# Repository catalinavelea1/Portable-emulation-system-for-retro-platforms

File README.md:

# Portable-emulation-system-for-retro-platforms

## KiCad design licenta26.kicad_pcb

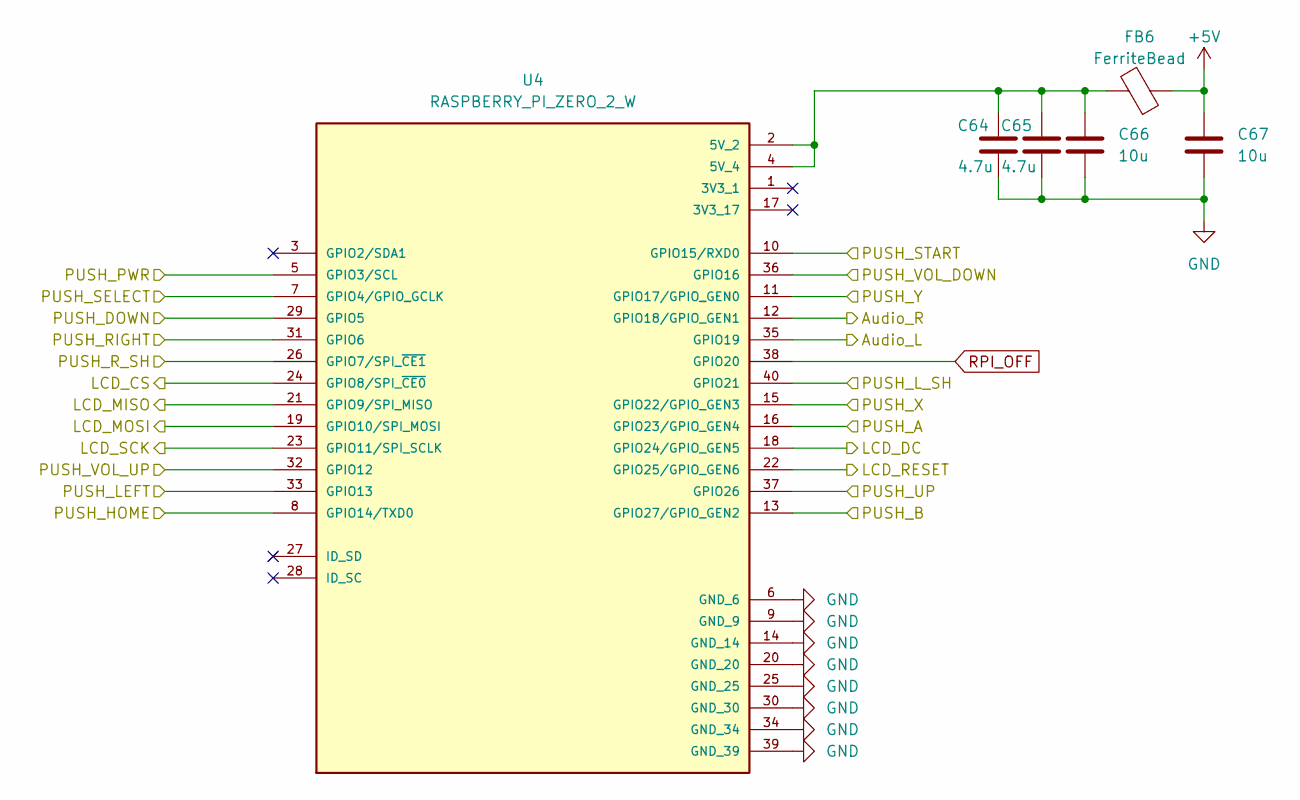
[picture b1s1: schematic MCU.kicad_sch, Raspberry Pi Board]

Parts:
C64, C65: 4.7u; C_1206_3216Metric_Pad1.33x1.80mm_HandSolder
C66, C67: 10u; C_1206_3216Metric_Pad1.33x1.80mm_HandSolder
FB6: FerriteBead; L_1206_3216Metric_Pad1.22x1.90mm_HandSolder
U4: RASPBERRY_PI_ZERO_2_W; MODULE_RASPBERRY_PI_ZERO_2_W; PARTREV April 2024

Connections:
/Audio_Sheet/Audio_L: U4.35 (GPIO19); also elsewhere on the board
/Audio_Sheet/Audio_R: U4.12 (GPIO18/GPIO_GEN1); also elsewhere on the board
/Buttons_Sheet/PUSH_A: U4.16 (GPIO23/GPIO_GEN4); also elsewhere on the board
/Buttons_Sheet/PUSH_B: U4.13 (GPIO27/GPIO_GEN2); also elsewhere on the board
/Buttons_Sheet/PUSH_DOWN: U4.29 (GPIO5); also elsewhere on the board
/Buttons_Sheet/PUSH_HOME: U4.8 (GPIO14/TXD0); also elsewhere on the board
/Buttons_Sheet/PUSH_LEFT: U4.33 (GPIO13); also elsewhere on the board
/Buttons_Sheet/PUSH_L_SH: U4.40 (GPIO21); also elsewhere on the board
/Buttons_Sheet/PUSH_RIGHT: U4.31 (GPIO6); also elsewhere on the board
/Buttons_Sheet/PUSH_R_SH: U4.26 (GPIO7/SPI_~CE1); also elsewhere on the board
/Buttons_Sheet/PUSH_SELECT: U4.7 (GPIO4/GPIO_GCLK); also elsewhere on the board
/Buttons_Sheet/PUSH_START: U4.10 (GPIO15/RXD0); also elsewhere on the board
/Buttons_Sheet/PUSH_UP: U4.37 (GPIO26); also elsewhere on the board
/Buttons_Sheet/PUSH_VOL_DOWN: U4.36 (GPIO16); also elsewhere on the board
/Buttons_Sheet/PUSH_VOL_UP: U4.32 (GPIO12); also elsewhere on the board
/Buttons_Sheet/PUSH_X: U4.15 (GPIO22/GPIO_GEN3); also elsewhere on the board
/Buttons_Sheet/PUSH_Y: U4.11 (GPIO17/GPIO_GEN0); also elsewhere on the board
/LCD_Sheet/LCD_CS: U4.24 (GPIO8/SPI_~CE0); also elsewhere on the board
/LCD_Sheet/LCD_DC: U4.18 (GPIO24/GPIO_GEN5); also elsewhere on the board
/LCD_Sheet/LCD_MISO: U4.21 (GPIO9/SPI_MISO); also elsewhere on the board
/LCD_Sheet/LCD_MOSI: U4.19 (GPIO10/SPI_MOSI); also elsewhere on the board
/LCD_Sheet/LCD_RESET: U4.22 (GPIO25/GPIO_GEN6); also elsewhere on the board
/LCD_Sheet/LCD_SCK: U4.23 (GPIO11/SPI_SCLK); also elsewhere on the board
/MCU/PUSH_PWR: U4.5 (GPIO3/SCL); also elsewhere on the board
GND: C64.2, C65.2, C66.2, C67.2, U4.6 (GND_6), U4.9 (GND_9), U4.14 (GND_14), U4.20 (GND_20), U4.25 (GND_25), U4.30 (GND_30), U4.34 (GND_34), U4.39 (GND_39); also elsewhere on the board
unnamed: C64.1, C65.1, C66.1, FB6.2, U4.2 (5V_2), U4.4 (5V_4)

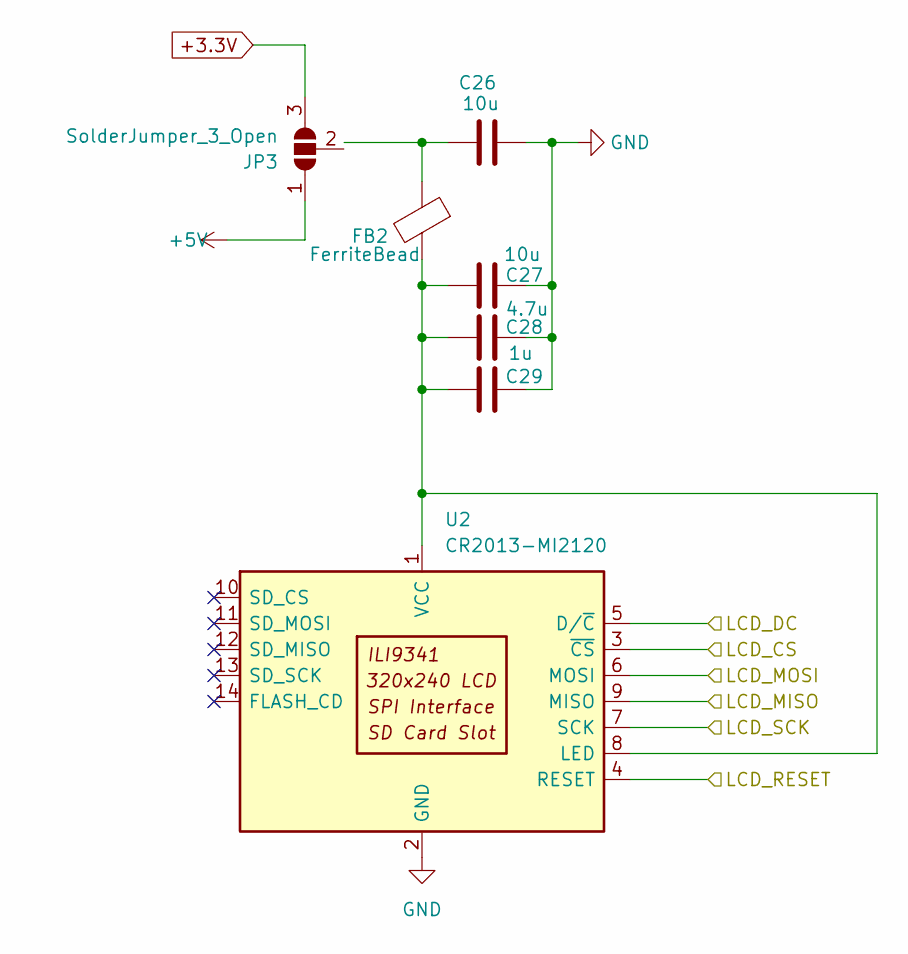
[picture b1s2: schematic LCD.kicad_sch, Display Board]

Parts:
C26, C27: 10u; C_1206_3216Metric_Pad1.33x1.80mm_HandSolder
C28: 4.7u; C_1206_3216Metric_Pad1.33x1.80mm_HandSolder
C29: 1u; C_1206_3216Metric_Pad1.33x1.80mm_HandSolder
FB2: FerriteBead; L_1206_3216Metric_Pad1.22x1.90mm_HandSolder
JP3: SolderJumper_3_Open; SolderJumper-3_P1.3mm_Open_RoundedPad1.0x1.5mm
U2: CR2013-MI2120; TFT-320x240

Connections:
+3.3V: JP3.3 (B); also elsewhere on the board
/LCD_Sheet/LCD_CS: U2.3 (~CS); also elsewhere on the board
/LCD_Sheet/LCD_DC: U2.5 (D/~C); also elsewhere on the board
/LCD_Sheet/LCD_MISO: U2.9 (MISO); also elsewhere on the board
/LCD_Sheet/LCD_MOSI: U2.6 (MOSI); also elsewhere on the board
/LCD_Sheet/LCD_RESET: U2.4 (RESET); also elsewhere on the board
/LCD_Sheet/LCD_SCK: U2.7 (SCK); also elsewhere on the board
GND: C26.2, C27.2, C28.2, C29.2, U2.2 (GND); also elsewhere on the board

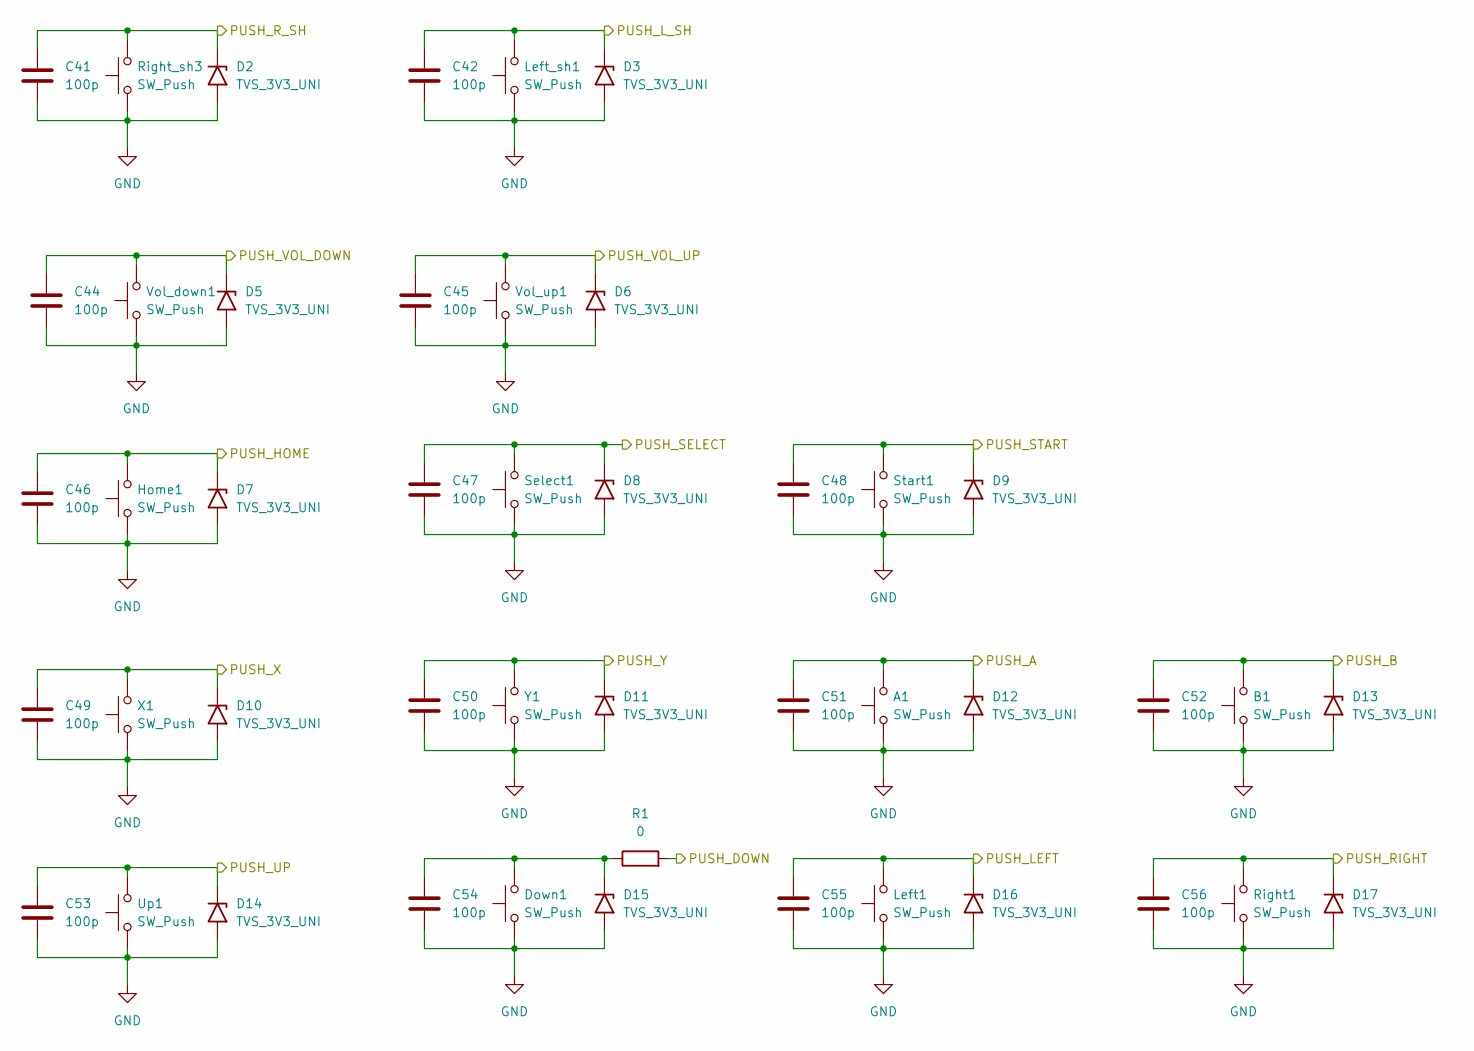
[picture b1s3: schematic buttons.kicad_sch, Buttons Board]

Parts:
A1: SW_Push; SW_PUSH_6mm
B1: SW_Push; SW_PUSH_6mm
C41, C42, C44, C45, C46, C47, C48, C49, C50, C51, C52, C53, C54, C55, C56: 100p; C_1206_3216Metric_Pad1.33x1.80mm_HandSolder
D2, D3, D5, D6, D7, D8, D9, D10, D11, D12, D13, D14, D15, D16, D17: TVS_3V3_UNI; D_SMA_Handsoldering
Down1: SW_Push; SW_PUSH_6mm
Home1: SW_Push; SW_PUSH_6mm
Left1: SW_Push; SW_PUSH_6mm
Left_sh1: SW_Push; SW_PUSH_6mm
R1: 0; R_1206_3216Metric_Pad1.30x1.75mm_HandSolder
Right1: SW_Push; SW_PUSH_6mm
Right_sh3: SW_Push; SW_PUSH_6mm
Select1: SW_Push; SW_PUSH_6mm
Start1: SW_Push; SW_PUSH_6mm
Up1: SW_Push; SW_PUSH_6mm
Vol_down1: SW_Push; SW_PUSH_6mm
Vol_up1: SW_Push; SW_PUSH_6mm
X1: SW_Push; SW_PUSH_6mm
Y1: SW_Push; SW_PUSH_6mm

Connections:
/Buttons_Sheet/PUSH_A: A1.2, C51.1, D12.1 (A1); also elsewhere on the board
/Buttons_Sheet/PUSH_B: B1.2, C52.1, D13.1 (A1); also elsewhere on the board
/Buttons_Sheet/PUSH_DOWN: R1.2; also elsewhere on the board
/Buttons_Sheet/PUSH_HOME: C46.1, D7.1 (A1), Home1.2; also elsewhere on the board
/Buttons_Sheet/PUSH_LEFT: C55.1, D16.1 (A1), Left1.2; also elsewhere on the board
/Buttons_Sheet/PUSH_L_SH: C42.1, D3.1 (A1), Left_sh1.2; also elsewhere on the board
/Buttons_Sheet/PUSH_RIGHT: C56.1, D17.1 (A1), Right1.2; also elsewhere on the board
/Buttons_Sheet/PUSH_R_SH: C41.1, D2.1 (A1), Right_sh3.2; also elsewhere on the board
/Buttons_Sheet/PUSH_SELECT: C47.1, D8.1 (A1), Select1.2; also elsewhere on the board
/Buttons_Sheet/PUSH_START: C48.1, D9.1 (A1), Start1.2; also elsewhere on the board
/Buttons_Sheet/PUSH_UP: C53.1, D14.1 (A1), Up1.2; also elsewhere on the board
/Buttons_Sheet/PUSH_VOL_DOWN: C44.1, D5.1 (A1), Vol_down1.2; also elsewhere on the board
/Buttons_Sheet/PUSH_VOL_UP: C45.1, D6.1 (A1), Vol_up1.2; also elsewhere on the board
/Buttons_Sheet/PUSH_X: C49.1, D10.1 (A1), X1.2; also elsewhere on the board
/Buttons_Sheet/PUSH_Y: C50.1, D11.1 (A1), Y1.2; also elsewhere on the board
GND: A1.1, B1.1, C41.2, C42.2, C44.2, C45.2, C46.2, C47.2, C48.2, C49.2, C50.2, C51.2, C52.2, C53.2, C54.2, C55.2, C56.2, D2.2 (A2), D3.2 (A2), D5.2 (A2), D6.2 (A2), D7.2 (A2), D8.2 (A2), D9.2 (A2), D10.2 (A2), D11.2 (A2), D12.2 (A2), D13.2 (A2), D14.2 (A2), D15.2 (A2), D16.2 (A2), D17.2 (A2), Down1.1, Home1.1, Left1.1, Left_sh1.1, Right1.1, Right_sh3.1, Select1.1, Start1.1, Up1.1, Vol_down1.1, Vol_up1.1, X1.1, Y1.1; also elsewhere on the board
unnamed: C54.1, D15.1 (A1), Down1.2, R1.1

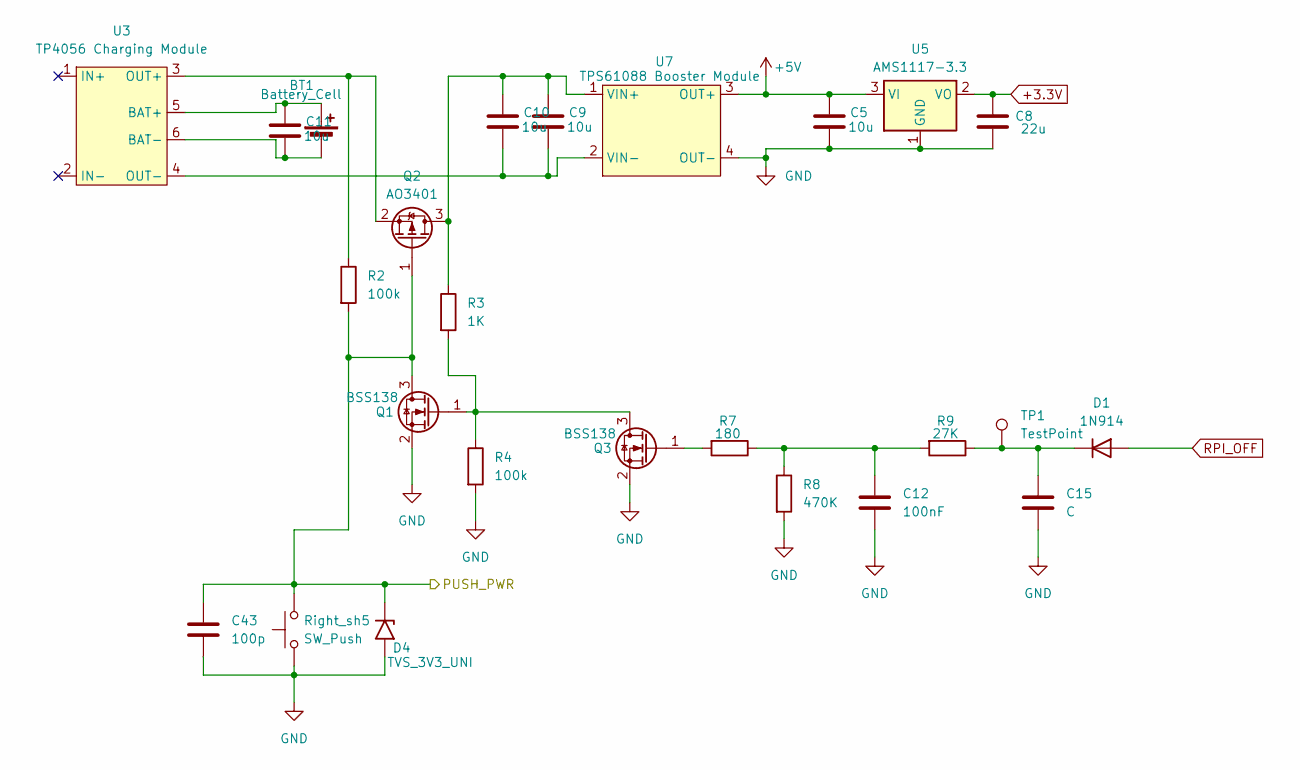
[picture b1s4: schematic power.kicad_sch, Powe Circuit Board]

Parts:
BT1: Battery_Cell; TerminalBlock_Phoenix_MKDS-1-2-3.81_1x02_P3.81mm_Horizontal
C5, C9, C10, C11: 10u; C_1206_3216Metric_Pad1.33x1.80mm_HandSolder
C8: 22u; C_1206_3216Metric_Pad1.33x1.80mm_HandSolder
C12: 100nF; C_1206_3216Metric_Pad1.33x1.80mm_HandSolder
C15: C
C43: 100p; C_1206_3216Metric_Pad1.33x1.80mm_HandSolder
D1: 1N914; D_DO-35_SOD27_P7.62mm_Horizontal
D4: TVS_3V3_UNI; D_SMA_Handsoldering
Q1, Q3: BSS138; SOT-23
Q2: AO3401; SOT-23
R2, R4: 100k; R_1206_3216Metric_Pad1.30x1.75mm_HandSolder
R3: 1K; R_1206_3216Metric_Pad1.30x1.75mm_HandSolder
R7: 180; R_1206_3216Metric_Pad1.30x1.75mm_HandSolder
R8: 470K; R_1206_3216Metric_Pad1.30x1.75mm_HandSolder
R9: 27K; R_1206_3216Metric_Pad1.30x1.75mm_HandSolder
Right_sh5: SW_Push; SW_PUSH_6mm
TP1: TestPoint; TestPoint_THTPad_D2.0mm_Drill1.0mm
U3: TP4056 Charging Module; TP4056-18650
U5: AMS1117-3.3; SOT-223-3_TabPin2
U7: TPS61088 Booster Module; hw-045

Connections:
+3.3V: C8.1, U5.2 (VO); also elsewhere on the board
/MCU/PUSH_PWR: C43.1, D4.1 (A1), Q1.3 (D), Q2.1 (G), R2.2, Right_sh5.2; also elsewhere on the board
GND: C5.2, C8.2, C12.2, C15.2, C43.2, D4.2 (A2), Q1.2 (S), Q3.2 (S), R4.2, R8.2, Right_sh5.1, U5.1 (GND), U7.4 (OUT-); also elsewhere on the board
unnamed: BT1.1 (+), C11.1, U3.5 (BAT+)
unnamed: BT1.2 (-), C11.2, U3.6 (BAT-)
unnamed: C12.1, R7.1, R8.1, R9.2
unnamed: Q1.1 (G), Q3.3 (D), R3.2, R4.1
unnamed: C9.1, C10.1, Q2.3 (D), R3.1, U7.1 (VIN+)
unnamed: Q2.2 (S), R2.1, U3.3 (OUT+)
unnamed: Q3.1 (G), R7.2
unnamed: C9.2, C10.2, U3.4 (OUT-), U7.2 (VIN-)

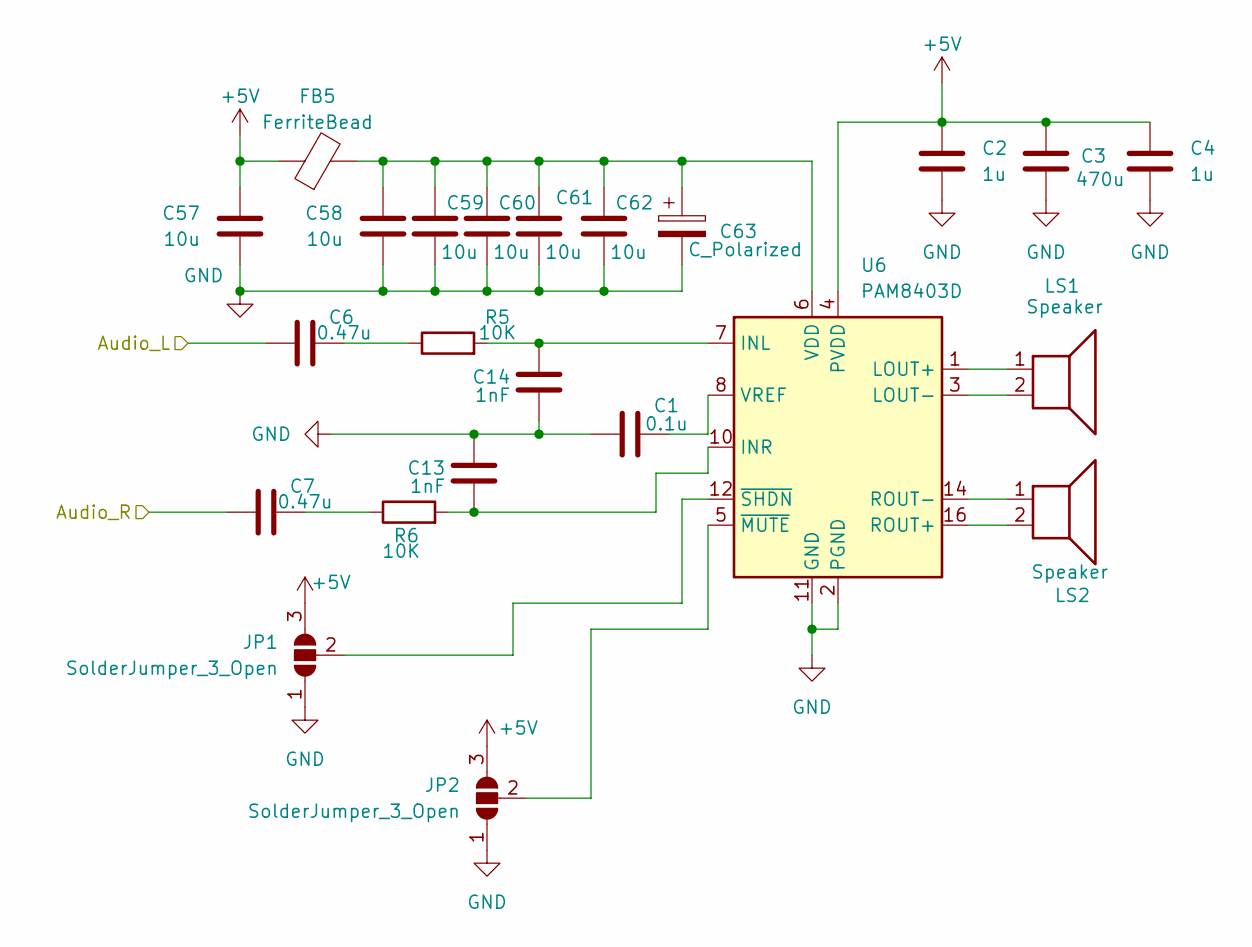
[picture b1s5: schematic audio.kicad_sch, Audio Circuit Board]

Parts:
C1: 0.1u; C_1206_3216Metric_Pad1.33x1.80mm_HandSolder
C2, C4: 1u; C_1206_3216Metric_Pad1.33x1.80mm_HandSolder
C3: 470u; C_1206_3216Metric_Pad1.33x1.80mm_HandSolder
C6, C7: 0.47u; C_1206_3216Metric_Pad1.33x1.80mm_HandSolder
C13, C14: 1nF; C_1206_3216Metric_Pad1.33x1.80mm_HandSolder
C57, C58, C59, C60, C61, C62: 10u; C_1206_3216Metric_Pad1.33x1.80mm_HandSolder
C63: C_Polarized; CP_EIA-2012-12_Kemet-R_HandSolder
FB5: FerriteBead; L_1206_3216Metric_Pad1.22x1.90mm_HandSolder
JP1, JP2: SolderJumper_3_Open; SolderJumper-3_P1.3mm_Open_RoundedPad1.0x1.5mm
LS1, LS2: Speaker; PinHeader_1x02_P2.54mm_Vertical
R5, R6: 10K; R_1206_3216Metric_Pad1.30x1.75mm_HandSolder
U6: PAM8403D; SOIC-16_3.9x9.9mm_P1.27mm

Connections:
/Audio_Sheet/Audio_L: C6.1; also elsewhere on the board
/Audio_Sheet/Audio_R: C7.1; also elsewhere on the board
GND: C1.2, C2.2, C3.2, C4.2, C13.1, C14.2, C57.2, C58.2, C59.2, C60.2, C61.2, C62.2, C63.2, JP1.1 (A), JP2.1 (A), U6.2 (PGND), U6.11 (GND), U6.15 (PGND); also elsewhere on the board
unnamed: C6.2, R5.1
unnamed: C7.2, R6.1
unnamed: JP1.2 (C), U6.12 (~SHDN)
unnamed: JP2.2 (C), U6.5 (~MUTE)
unnamed: C14.1, R5.2, U6.7 (INL)
unnamed: C13.2, R6.2, U6.10 (INR)
unnamed: LS1.1, U6.1 (LOUT+)
unnamed: LS1.2, U6.3 (LOUT-)
unnamed: LS2.2, U6.16 (ROUT+)
unnamed: LS2.1, U6.14 (ROUT-)
unnamed: C58.1, C59.1, C60.1, C61.1, C62.1, C63.1, FB5.2, U6.6 (VDD)
unnamed: C1.1, U6.8 (VREF)

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
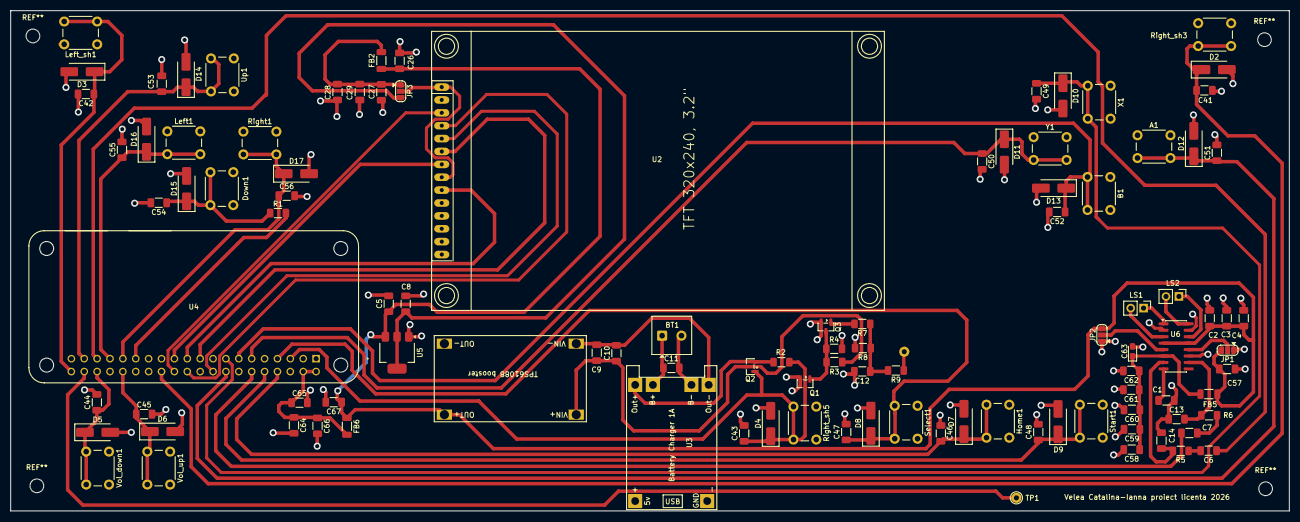
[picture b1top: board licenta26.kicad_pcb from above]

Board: 2 copper layers, 252.2 x 98.6 mm, 105 parts (0 on the bottom side), 52 nets.
